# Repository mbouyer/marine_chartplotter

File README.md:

Hardware and software for an opencpn-based chartplotter
The kardware has been designed with kicad 4.0.x
The chartplotter is built around a A20-based single-board computer
from Olimex (https://www.olimex.com/Products/OLinuXino/A20/A20-OLinuXIno-LIME2/)
and a 15" TFT full HD display also from Olimex
(https://www.olimex.com/Products/OLinuXino/LCD/LCD-OLinuXino-15.6FHD)

The hardware consist of 4 boards
- a breakout board for the Lime2, also providing power supplies,
  an audio amplifier, RS422 and CAN interfaces, and a I2C connection to
  a PIC18 for power management and TOD clock.
- a board holding buttons
- a board holding a GPS module
- a board for connections to other electronic equipements (VHF, sensors, ...)
  via a single flat cable.

for more details see the wiki: https://github.com/mbouyer/marine_chartplotter/wiki

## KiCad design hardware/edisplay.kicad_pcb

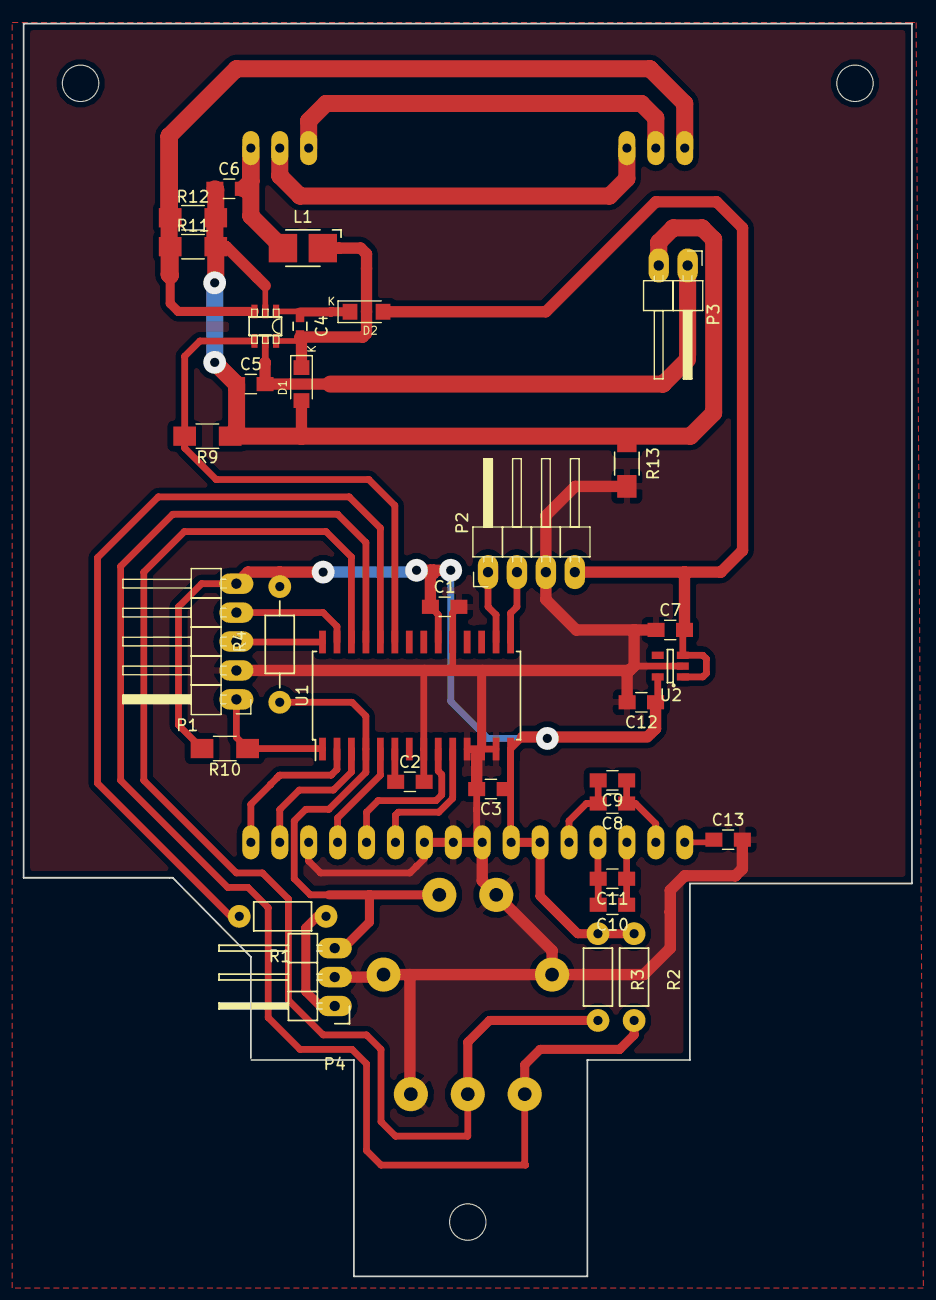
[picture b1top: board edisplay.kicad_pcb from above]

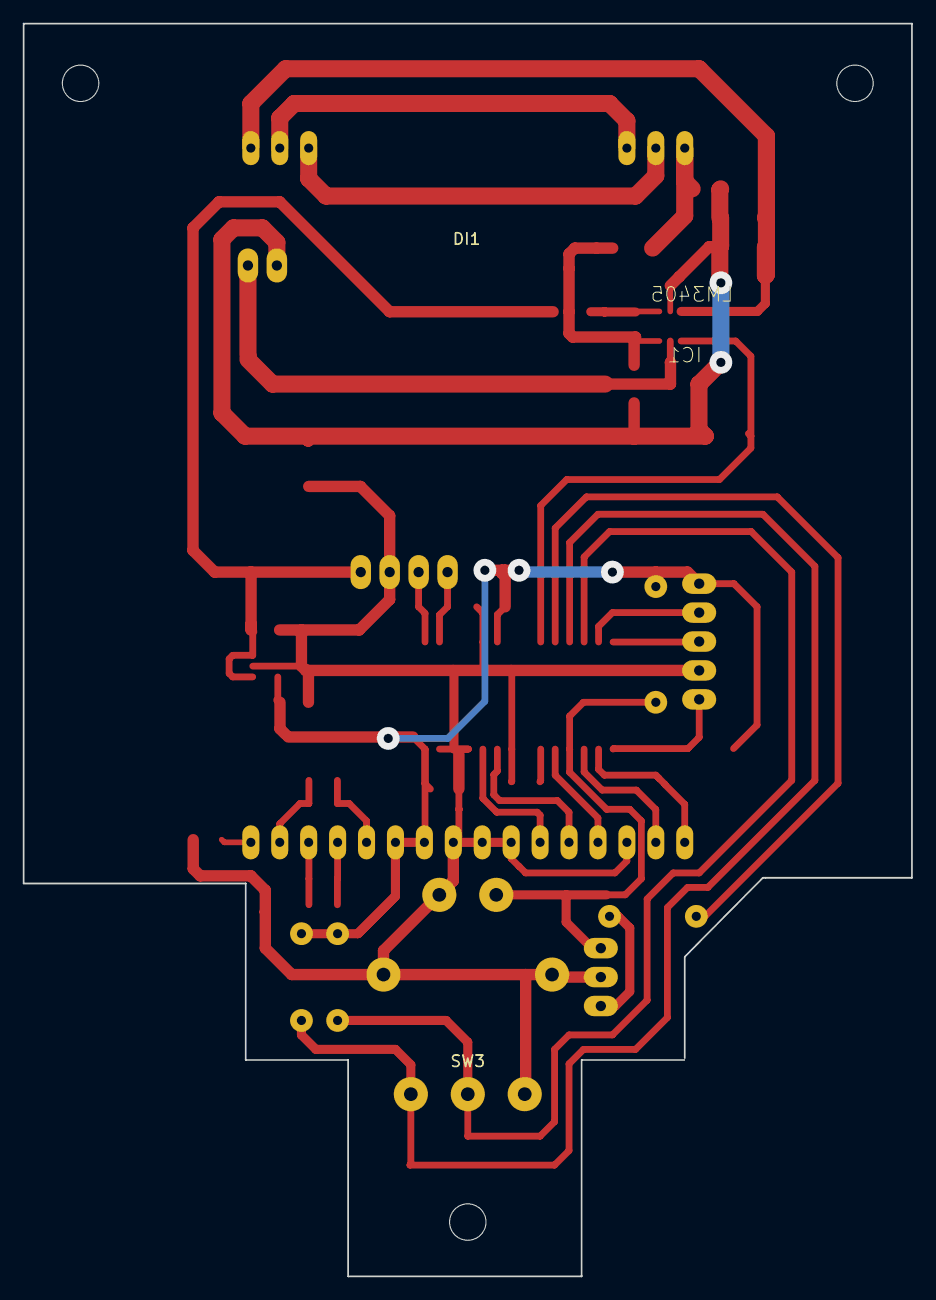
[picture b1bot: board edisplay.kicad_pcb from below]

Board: 2 copper layers, 78.0 x 110.0 mm, 34 parts (2 on the bottom side), 33 nets.

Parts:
C1, C3, C5, C6, C7, C8, C9, C10, C11, C12, C13: 1µF; C_0805_HandSoldering
C2: 10µF; C_0805_HandSoldering
C4: 0.1µF; C_0603_HandSoldering
D1, D2: SL02; DO-219AB
DI1: EADOGXL160-7
IC1: LM3405; texas-local-SOT23-06
L1: 68µH; Inductor_1212
P1: CONN_01X05; Pin_Header_Angled_1x05_Pitch2.54mm
P2: CONN_01X04; Pin_Header_Angled_1x04_Pitch2.54mm
P3: CONN_01X02; Pin_Header_Angled_1x02_Pitch2.54mm
P4: CONN_01X03; Pin_Header_Angled_1x03
R1: 330; Resistor_Horizontal_RM7mm
R2, R3: 10K; Resistor_Horizontal_RM7mm
R4: 10K; Resistor_Horizontal_RM10mm
R9: 10K; R_1206_HandSoldering
R10: 1K; R_1206_HandSoldering
R11, R12: 5.1; R_1206_HandSoldering
R13: 330; R_1206_HandSoldering
SW3: ROTARY_ENCODER_SWITCH; PEC16_S
U1: PIC18F26J53; SOIC-28W_7.5x17.9mm_Pitch1.27mm
U2: LP3990MF; SOT-23-5

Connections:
+3V3: C1.1, C3.1, C12.1, DI1.22, DI1.23, P1.5, R2.1, R3.1, R4.2, R10.2, U1.14, U1.20, U2.5
+5V: C7.2, D2.2, P2.4, U2.1, U2.3
+12V: C5.2, IC1.5, P3.1
GND: C1.2, C2.2, C3.2, C7.1, C12.2, C13.2, DI1.24, DI1.25, DI1.26, DI1.30, P1.2, P2.3, P4.2, R13.2, SW3.2, SW3.4, U1.8, U1.11, U1.12, U1.13, U1.19, U2.2
GNDA: C5.1, C6.1, D1.2, IC1.2, P3.2, R9.1, R11.2, R12.2, R13.1
unnamed: C2.1, U1.6
unnamed: C4.1, D2.1, IC1.1
unnamed: C4.2, D1.1, IC1.6, L1.1
unnamed: C6.2, DI1.1, L1.2
unnamed: C8.1, C9.1, DI1.18
unnamed: C8.2, C9.2, DI1.21
unnamed: C10.1, C11.1, DI1.19
unnamed: C10.2, C11.2, DI1.20
unnamed: C13.1, DI1.17
unnamed: DI1.2, DI1.14
unnamed: DI1.3, DI1.15
unnamed: DI1.16, IC1.3, R11.1, R12.1
unnamed: DI1.27, U1.10
unnamed: DI1.28, U1.9
unnamed: DI1.29, U1.5
unnamed: DI1.31, U1.3
unnamed: DI1.32, U1.2
unnamed: IC1.4, R9.2, U1.23
unnamed: P1.1, R10.1, U1.1
unnamed: P1.3, U1.28
unnamed: P1.4, U1.27
unnamed: P2.1, U1.16
unnamed: P2.2, U1.15
unnamed: P4.1, R1.1
unnamed: P4.3, R4.1, SW3.5, U1.4
unnamed: R1.2, U1.24
unnamed: R2.2, SW3.1, U1.25
unnamed: R3.2, SW3.3, U1.26

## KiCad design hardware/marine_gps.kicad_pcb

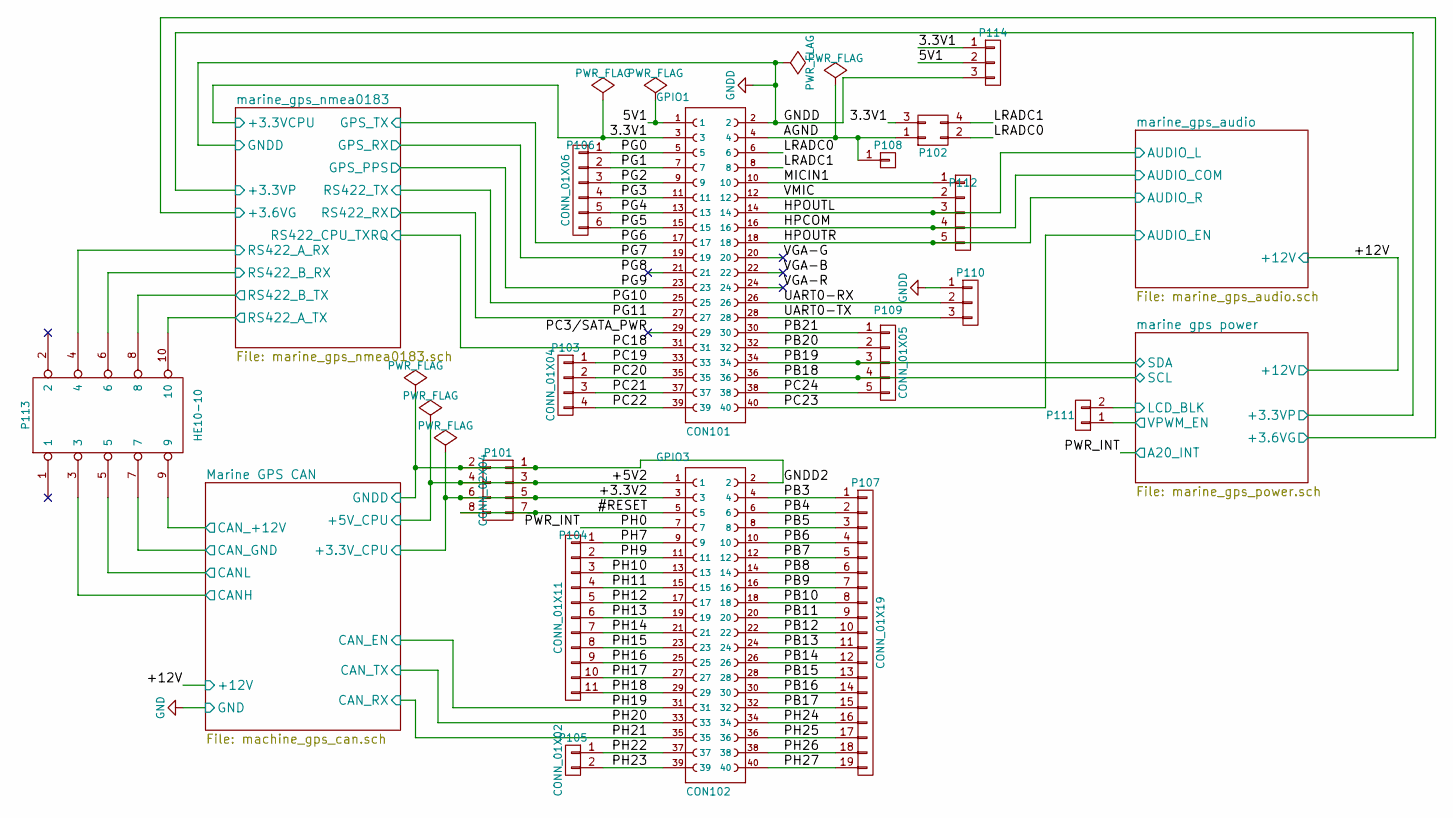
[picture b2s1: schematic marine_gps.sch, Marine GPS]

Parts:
CON101: GPIO1; A10_OLIMEXINO_LIME_SHIELD_1-YA-V36P-2X20-LF
CON102: GPIO3; A10_OLIMEXINO_LIME_SHIELD_1-YA-V36P-2X20-LF
P101: CONN_02X04; Pin_Header_Angled_2x04
P102: CONN_02X02; Pin_Header_Angled_2x02
P103: CONN_01X04; Pin_Header_Straight_1x04
P104: CONN_01X11; Pin_Header_Straight_1x11
P105, P111: CONN_01X02; Pin_Header_Straight_1x02
P106: CONN_01X06; Pin_Header_Straight_1x06
P107: CONN_01X19; Pin_Header_Straight_1x19
P108: CONN_01X01; Pin_Header_Straight_1x01
P109, P112: CONN_01X05; Pin_Header_Straight_1x05
P110: CONN_01X03; Pin_Header_Straight_1x03
P113: HE10-10; HE10-10C
P114: CONN_01X03; Pin_Header_Angled_1x03

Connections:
/5V1: CON101.1, P114.2
/#RESET: CON102.5, P101.7, P101.8
/AGND: CON101.4, P102.1, P108.1
/LRADC0: CON101.6, P102.2
/LRADC1: CON101.8, P102.4
/MICIN1: CON101.10, P112.1
/Marine GPS CAN/+3.3V_CPU: CON102.3, P101.5, P101.6; also elsewhere on the board
/Marine GPS CAN/+5V_CPU: CON102.1, P101.3, P101.4; also elsewhere on the board
/Marine GPS CAN/CANH: P113.3; also elsewhere on the board
/Marine GPS CAN/CANL: P113.5; also elsewhere on the board
/Marine GPS CAN/CAN_+12V: P113.9; also elsewhere on the board
/Marine GPS CAN/CAN_EN: CON102.31; also elsewhere on the board
/Marine GPS CAN/CAN_RX: CON102.35; also elsewhere on the board
/Marine GPS CAN/CAN_TX: CON102.33; also elsewhere on the board
/Marine GPS CAN/GNDD: CON102.2, P101.1, P101.2; also elsewhere on the board
/PB3: CON102.4, P107.1
/PB4: CON102.6, P107.2
/PB5: CON102.8, P107.3
/PB6: CON102.10, P107.4
/PB7: CON102.12, P107.5
/PB8: CON102.14, P107.6
/PB9: CON102.16, P107.7
/PB10: CON102.18, P107.8
/PB11: CON102.20, P107.9
/PB12: CON102.22, P107.10
/PB13: CON102.24, P107.11
/PB14: CON102.26, P107.12
/PB15: CON102.28, P107.13
/PB16: CON102.30, P107.14
/PB17: CON102.32, P107.15
/PB20: CON101.32, P109.2
/PB21: CON101.30, P109.1
/PC3/SATA_PWR: CON101.29
/PC19: CON101.33, P103.1
/PC20: CON101.35, P103.2
/PC21: CON101.37, P103.3
/PC22: CON101.39, P103.4
/PC24: CON101.38, P109.5
/PG0: CON101.5, P106.1
/PG1: CON101.7, P106.2
/PG2: CON101.9, P106.3
/PG3: CON101.11, P106.4
/PG4: CON101.13, P106.5
/PG5: CON101.15, P106.6
/PG8: CON101.21
/PH7: CON102.9, P104.1
/PH9: CON102.11, P104.2
/PH10: CON102.13, P104.3
/PH11: CON102.15, P104.4
/PH12: CON102.17, P104.5
/PH13: CON102.19, P104.6
/PH14: CON102.21, P104.7
/PH15: CON102.23, P104.8
/PH16: CON102.25, P104.9
/PH17: CON102.27, P104.10
/PH18: CON102.29, P104.11
/PH22: CON102.37, P105.1
/PH23: CON102.39, P105.2
/PH24: CON102.34, P107.16
/PH25: CON102.36, P107.17
/PH26: CON102.38, P107.18
/PH27: CON102.40, P107.19
/UART0-RX: CON101.26, P110.2
/UART0-TX: CON101.28, P110.3
/VGA-B: CON101.22
/VGA-G: CON101.20
/VGA-R: CON101.24
/VMIC: CON101.12, P112.2
/marine gps power/A20_INT: CON102.7; also elsewhere on the board
/marine gps power/LCD_BLK: P111.2; also elsewhere on the board
/marine gps power/SCL: CON101.36, P109.4; also elsewhere on the board
/marine gps power/SDA: CON101.34, P109.3; also elsewhere on the board
/marine gps power/VPWM_EN: P111.1; also elsewhere on the board
/marine_gps_audio/AUDIO_COM: CON101.16, P112.4; also elsewhere on the board
/marine_gps_audio/AUDIO_EN: CON101.40; also elsewhere on the board
/marine_gps_audio/AUDIO_L: CON101.14, P112.3; also elsewhere on the board
/marine_gps_audio/AUDIO_R: CON101.18, P112.5; also elsewhere on the board
/marine_gps_nmea0183/GPS_PPS: CON101.23; also elsewhere on the board
/marine_gps_nmea0183/GPS_RX: CON101.19; also elsewhere on the board
/marine_gps_nmea0183/GPS_TX: CON101.17; also elsewhere on the board
/marine_gps_nmea0183/RS422_A_RX: P113.4; also elsewhere on the board
/marine_gps_nmea0183/RS422_A_TX: P113.10; also elsewhere on the board
/marine_gps_nmea0183/RS422_B_RX: P113.6; also elsewhere on the board
/marine_gps_nmea0183/RS422_B_TX: P113.8; also elsewhere on the board
/marine_gps_nmea0183/RS422_CPU_TXRQ: CON101.31; also elsewhere on the board
/marine_gps_nmea0183/RS422_RX: CON101.27; also elsewhere on the board
/marine_gps_nmea0183/RS422_TX: CON101.25; also elsewhere on the board
GND: P113.7; also elsewhere on the board
GND2: CON101.2, P110.1, P114.3; also elsewhere on the board
VCC2: CON101.3, P102.3, P114.1; also elsewhere on the board

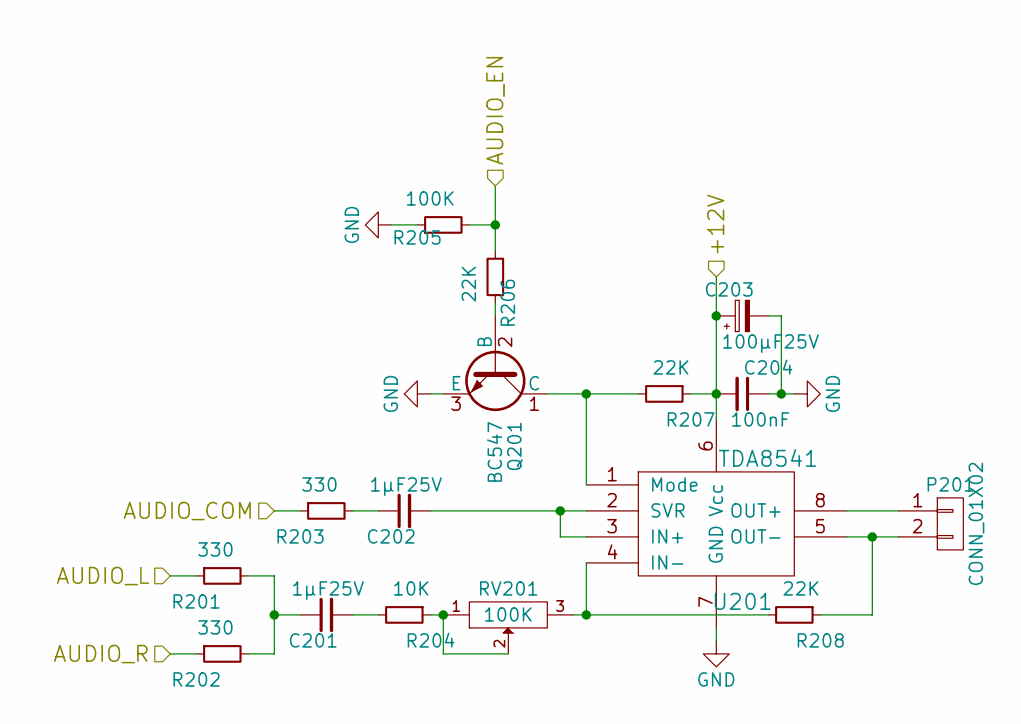
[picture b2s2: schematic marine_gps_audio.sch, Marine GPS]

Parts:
C201, C202: 1µF25V; C_0805
C203: 100µF25V; C_Radial_D6.3_L11.2_P2.5
C204: 100nF; C_0805
P201: CONN_01X02; Pin_Header_Straight_1x02
Q201: BC547; TO-92_Molded_Narrow
R201, R202, R203: 330; Resistor_Horizontal_RM15mm
R204: 10K; Resistor_Horizontal_RM15mm
R205: 100K; Resistor_Horizontal_RM10mm
R206: 22K; Resistor_Horizontal_RM10mm
R207, R208: 22K; Resistor_Horizontal_RM15mm
RV201: 100K; CB10LV
U201: TDA8541; SOIC-8-N

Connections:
+12V: C203.1, C204.2, R207.1, U201.6 (Vcc); also elsewhere on the board
/marine_gps_audio/AUDIO_COM: R203.1; also elsewhere on the board
/marine_gps_audio/AUDIO_EN: R205.2, R206.2; also elsewhere on the board
/marine_gps_audio/AUDIO_L: R201.1; also elsewhere on the board
/marine_gps_audio/AUDIO_R: R202.1; also elsewhere on the board
GND: C203.2, C204.1, Q201.3 (E), R205.1, U201.7 (GND); also elsewhere on the board
unnamed: C201.1, R201.2, R202.2
unnamed: C201.2, R204.2
unnamed: C202.1, R203.2
unnamed: C202.2, U201.2 (SVR), U201.3 (IN+)
unnamed: P201.1, U201.8 (OUT+)
unnamed: P201.2, R208.1, U201.5 (OUT-)
unnamed: Q201.1 (C), R207.2, U201.1 (Mode)
unnamed: Q201.2 (B), R206.1
unnamed: R204.1, RV201.1, RV201.2
unnamed: R208.2, RV201.3, U201.4 (IN-)

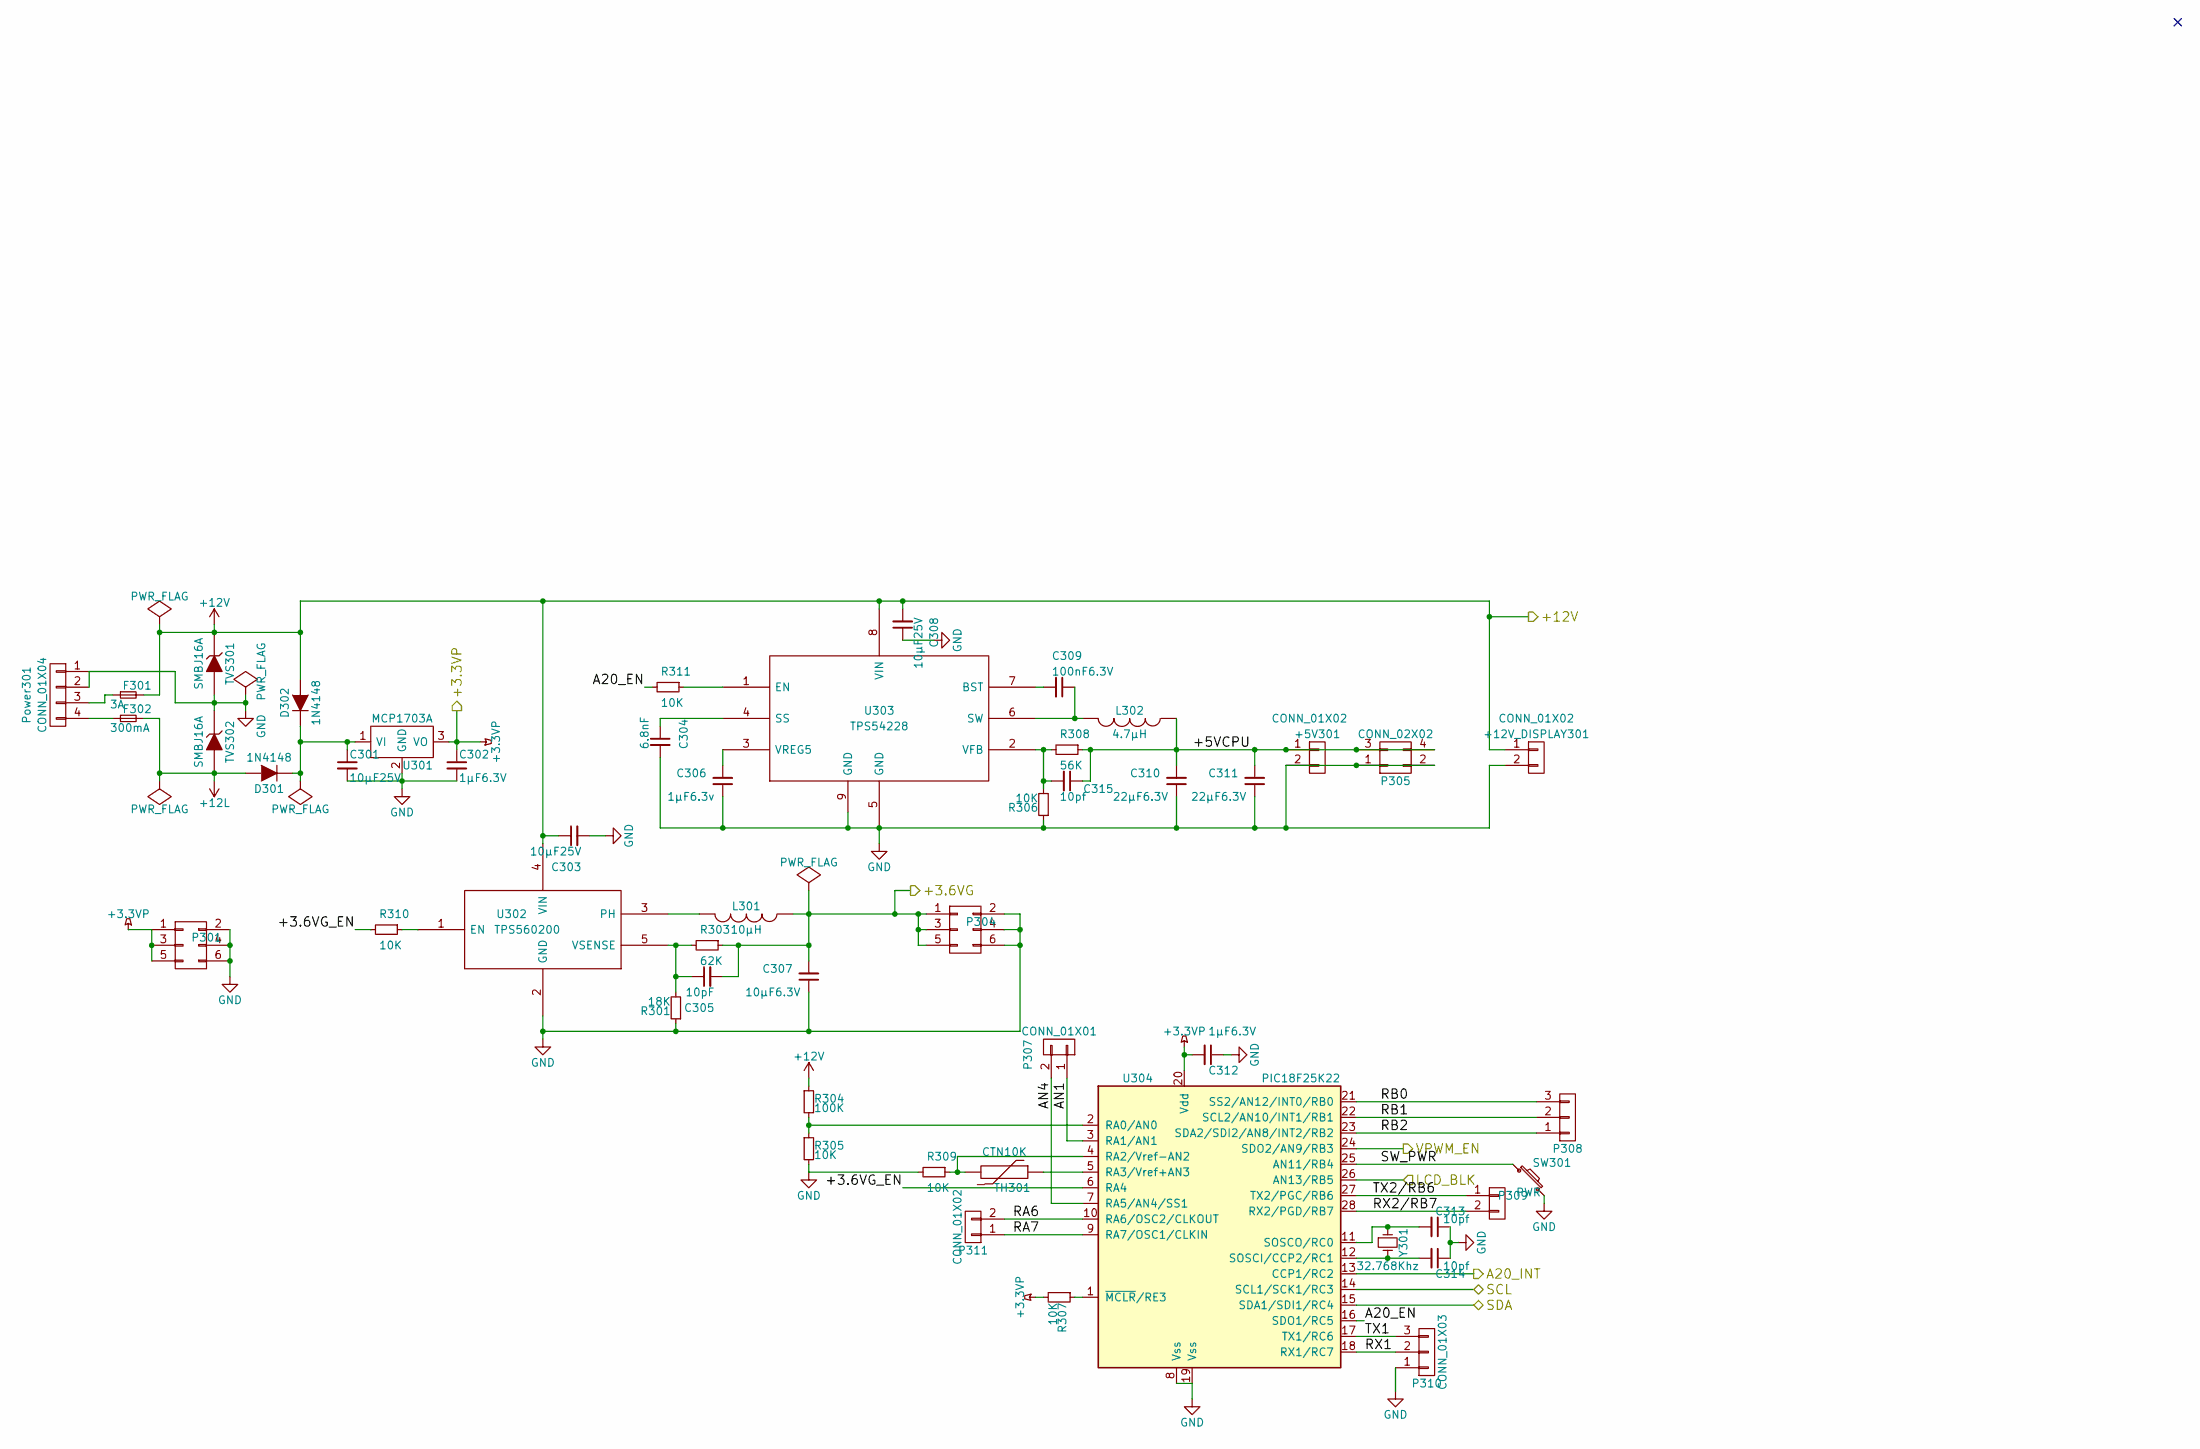
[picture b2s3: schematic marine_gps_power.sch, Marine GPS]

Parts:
+5V301, +12V_DISPLAY301: CONN_01X02; Pin_Header_Straight_1x02
C301, C303, C308: 10µF25V; C_1210
C302, C312: 1µF6.3V; C_0805
C304: 6.8nF; C_0603_HandSoldering
C305: 10pF; C_0603_HandSoldering
C306: 1µF6.3v; C_0805
C307: 10µF6.3V; C_1210
C309: 100nF6.3V; C_0805
C310, C311: 22µF6.3V; C_1210
C313, C314, C315: 10pf; C_0603_HandSoldering
D301, D302: 1N4148; Diode_DO-35_SOD27_Horizontal_RM10
F301: 3A; Fuseholder5x20_horiz_SemiClosed_Casing10x22.5mm
F302: 300mA; Fuseholder5x20_horiz_SemiClosed_Casing10x22.5mm
L301: 10µH; Choke_SMD_7.3x7.3_H4.5
L302: 4.7µH; Choke_SMD_10.4x10.4_H4.8
P301, P304: CONN_02X03; Pin_Header_Angled_2x03
P305: CONN_02X02; Pin_Header_Angled_2x02
P307: CONN_01X01; Pin_Header_Straight_1x02
P308, P310: CONN_01X03; Pin_Header_Angled_1x03
P309, P311: CONN_01X02; Pin_Header_Straight_1x02
Power301: CONN_01X04; minifit-4
R301: 18K; Resistor_Horizontal_RM15mm
R303: 62K; Resistor_Horizontal_RM15mm
R304: 100K; Resistor_Horizontal_RM10mm
R305, R310, R311: 10K; Resistor_Horizontal_RM10mm
R306, R307: 10K; R_1210_HandSoldering
R308: 56K; R_1210_HandSoldering
R309: 10K; Resistor_Horizontal_RM15mm
SW301: PWR; Pin_Header_Angled_1x02
TH301: CTN10K; Pin_Header_Straight_1x02
TVS301, TVS302: SMBJ16A; DO-214AB
U301: MCP1703A; SOT-223-Tto2
U302: TPS560200; SOT-23-5
U303: TPS54228; SOIC-8-1EP_3.9x4.9mm_Pitch1.27mm
U304: PIC18F25K22; DIP-28_W7.62mm_LongPads
Y301: 32.768Khz; CMR200T

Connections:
+3.3VP: C302.1, C312.2, P301.1, P301.3, P301.5, R307.2, U301.3 (VO), U304.20 (Vdd); also elsewhere on the board
+12L: D301.2 (A), F302.2, TVS302.2 (A)
+12V: +12V_DISPLAY301.1, C303.1, C308.2, D302.2 (A), F301.2, R304.1, TVS301.1 (K), U302.4 (VIN), U303.8 (VIN); also elsewhere on the board
/marine gps power/+3.6VG_EN: R310.2, U304.6 (RA4)
/marine gps power/+5VCPU: +5V301.1, C310.2, C311.2, C315.1, L302.1, P305.3, P305.4, R308.1
/marine gps power/A20_EN: R311.2, U304.16 (SDO1/RC5)
/marine gps power/A20_INT: U304.13 (CCP1/RC2); also elsewhere on the board
/marine gps power/AN1: P307.1, U304.3 (RA1/AN1)
/marine gps power/AN4: P307.2, U304.7 (RA5/AN4/SS1)
/marine gps power/LCD_BLK: U304.26 (AN13/RB5); also elsewhere on the board
/marine gps power/RA6: P311.2, U304.10 (RA6/OSC2/CLKOUT)
/marine gps power/RA7: P311.1, U304.9 (RA7/OSC1/CLKIN)
/marine gps power/RB0: P308.3, U304.21 (SS2/AN12/INT0/RB0)
/marine gps power/RB1: P308.2, U304.22 (SCL2/AN10/INT1/RB1)
/marine gps power/RB2: P308.1, U304.23 (SDA2/SDI2/AN8/INT2/RB2)
/marine gps power/RX1: P310.2, U304.18 (RX1/RC7)
/marine gps power/RX2/RB7: P309.2, U304.28 (RX2/PGD/RB7)
/marine gps power/SCL: U304.14 (SCL1/SCK1/RC3); also elsewhere on the board
/marine gps power/SDA: U304.15 (SDA1/SDI1/RC4); also elsewhere on the board
/marine gps power/SW_PWR: SW301.1, U304.25 (AN11/RB4)
/marine gps power/TX1: P310.3, U304.17 (TX1/RC6)
/marine gps power/TX2/RB6: P309.1, U304.27 (TX2/PGC/RB6)
/marine gps power/VPWM_EN: U304.24 (SDO2/AN9/RB3); also elsewhere on the board
GND: +5V301.2, +12V_DISPLAY301.2, C301.2, C302.2, C303.2, C304.2, C306.1, C307.1, C308.1, C310.1, C311.1, C312.1, C313.1, C314.1, P301.2, P301.4, P301.6, P304.2, P304.4, P304.6, P305.1, P305.2, P310.1, Power301.1, Power301.2, R301.1, R305.2, R306.1, R309.2, SW301.2, TVS301.2 (A), TVS302.1 (K), U301.2 (GND), U302.2 (GND), U303.5 (GND), U303.9 (GND), U304.8 (Vss), U304.19 (Vss); also elsewhere on the board
unnamed: C301.1, D301.1 (K), D302.1 (K), U301.1 (VI)
unnamed: C304.1, U303.4 (SS)
unnamed: C305.1, R301.2, R303.2, U302.5 (VSENSE)
unnamed: C306.2, U303.3 (VREG5)
unnamed: C309.1, L302.2, U303.6 (SW)
unnamed: C309.2, U303.7 (BST)
unnamed: C313.2, U304.11 (SOSCO/RC0), Y301.1
unnamed: C314.2, U304.12 (SOSCI/CCP2/RC1), Y301.2
unnamed: C315.2, R306.2, R308.2, U303.2 (VFB)
unnamed: F301.1, Power301.3
unnamed: F302.1, Power301.4
unnamed: L301.2, U302.3 (PH)
unnamed: R304.2, R305.1, U304.2 (RA0/AN0)
unnamed: R307.1, U304.1 (~MCLR~/RE3)
unnamed: R309.1, TH301.2, U304.4 (RA2/Vref-AN2)
unnamed: R310.1, U302.1 (EN)
unnamed: R311.1, U303.1 (EN)
unnamed: TH301.1, U304.5 (RA3/Vref+AN3)
VCC: C305.2, C307.2, L301.1, P304.1, P304.3, P304.5, R303.1; also elsewhere on the board

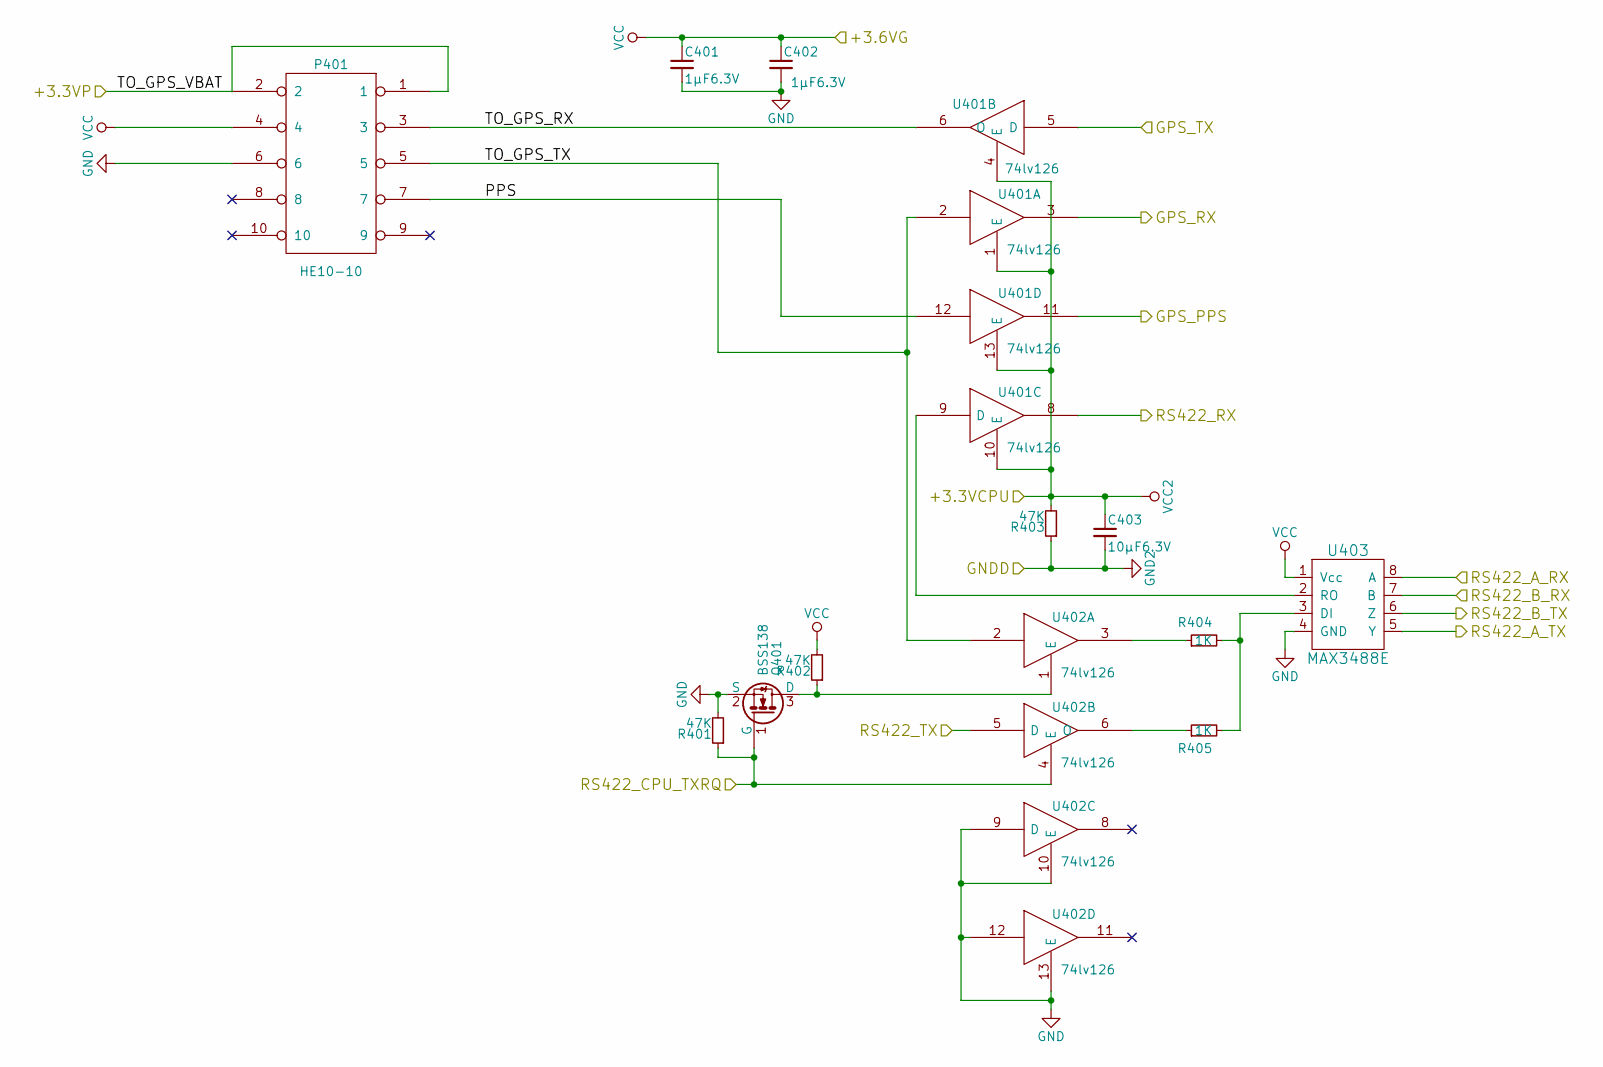
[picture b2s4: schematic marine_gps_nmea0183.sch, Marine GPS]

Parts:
C401, C402: 1µF6.3V; C_1210
C403: 10µF6.3V; C_1210
P401: HE10-10; HE10-10C
Q401: BSS138; SOT-23
R401, R402, R403: 47K; Resistor_Horizontal_RM15mm
R404, R405: 1K; Resistor_Horizontal_RM15mm
U401, U402: 74lv126; SOIC-14_3.9x8.7mm_Pitch1.27mm
U403: MAX3488E; SOIC-8_3.9x4.9mm_Pitch1.27mm

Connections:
+3.3VP: P401.1, P401.2; also elsewhere on the board
/marine_gps_nmea0183/GPS_PPS: U401.11; also elsewhere on the board
/marine_gps_nmea0183/GPS_RX: U401.3; also elsewhere on the board
/marine_gps_nmea0183/GPS_TX: U401.5 (D); also elsewhere on the board
/marine_gps_nmea0183/PPS: P401.7, U401.12
/marine_gps_nmea0183/RS422_A_RX: U403.8 (A); also elsewhere on the board
/marine_gps_nmea0183/RS422_A_TX: U403.5 (Y); also elsewhere on the board
/marine_gps_nmea0183/RS422_B_RX: U403.7 (B); also elsewhere on the board
/marine_gps_nmea0183/RS422_B_TX: U403.6 (Z); also elsewhere on the board
/marine_gps_nmea0183/RS422_CPU_TXRQ: Q401.1 (G), R401.1, U402.4 (E); also elsewhere on the board
/marine_gps_nmea0183/RS422_RX: U401.8; also elsewhere on the board
/marine_gps_nmea0183/RS422_TX: U402.5 (D); also elsewhere on the board
/marine_gps_nmea0183/TO_GPS_RX: P401.3, U401.6 (O)
/marine_gps_nmea0183/TO_GPS_TX: P401.5, U401.2, U402.2
GND: C401.2, C402.2, P401.6, Q401.2 (S), R401.2, U402.7 (GND), U402.9 (D), U402.10 (E), U402.12, U402.13 (E), U403.4 (GND); also elsewhere on the board
GND2: C403.2, R403.1, U401.7 (GND2); also elsewhere on the board
unnamed: Q401.3 (D), R402.1, U402.1 (E)
unnamed: R404.1, U402.3
unnamed: R404.2, R405.2, U403.3 (DI)
unnamed: R405.1, U402.6 (O)
unnamed: U401.9 (D), U403.2 (RO)
VCC: C401.1, C402.1, P401.4, R402.2, U402.14 (VCC), U403.1 (Vcc); also elsewhere on the board
VCC2: C403.1, R403.2, U401.1 (E), U401.4 (E), U401.10 (E), U401.13 (E), U401.14 (VCC2); also elsewhere on the board

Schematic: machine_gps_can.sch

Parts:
C501, C502: 1µF6.3V; C_0805
P501: CONN_01X02; Pin_Header_Straight_1x02
Q501, Q502: BSS138; SOT-23
Q503: DMG2307L; SOT-23
R501: 47K; Resistor_Horizontal_RM15mm
R502: 47K; Resistor_Horizontal_RM10mm
U501: MCP2562; DIP-8_W7.62mm

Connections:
+12V: Q503.2, R502.1; also elsewhere on the board
/Marine GPS CAN/+3.3V_CPU: C502.2, U501.5 (VIO); also elsewhere on the board
/Marine GPS CAN/+5V_CPU: C501.1, U501.3 (VDD); also elsewhere on the board
/Marine GPS CAN/CANH: U501.7 (CANH); also elsewhere on the board
/Marine GPS CAN/CANL: U501.6 (CANL); also elsewhere on the board
/Marine GPS CAN/CAN_+12V: P501.2; also elsewhere on the board
/Marine GPS CAN/CAN_EN: Q501.1 (G), Q502.1 (G), R501.2; also elsewhere on the board
/Marine GPS CAN/CAN_RX: U501.4 (RXD); also elsewhere on the board
/Marine GPS CAN/CAN_TX: U501.1 (TXD); also elsewhere on the board
/Marine GPS CAN/GNDD: C501.2, C502.1, Q501.2 (S), Q502.2 (S), R501.1, U501.2 (VSS); also elsewhere on the board
unnamed: P501.1, Q503.3
unnamed: Q501.3 (D), U501.8 (STB)
unnamed: Q502.3 (D), Q503.1, R502.2

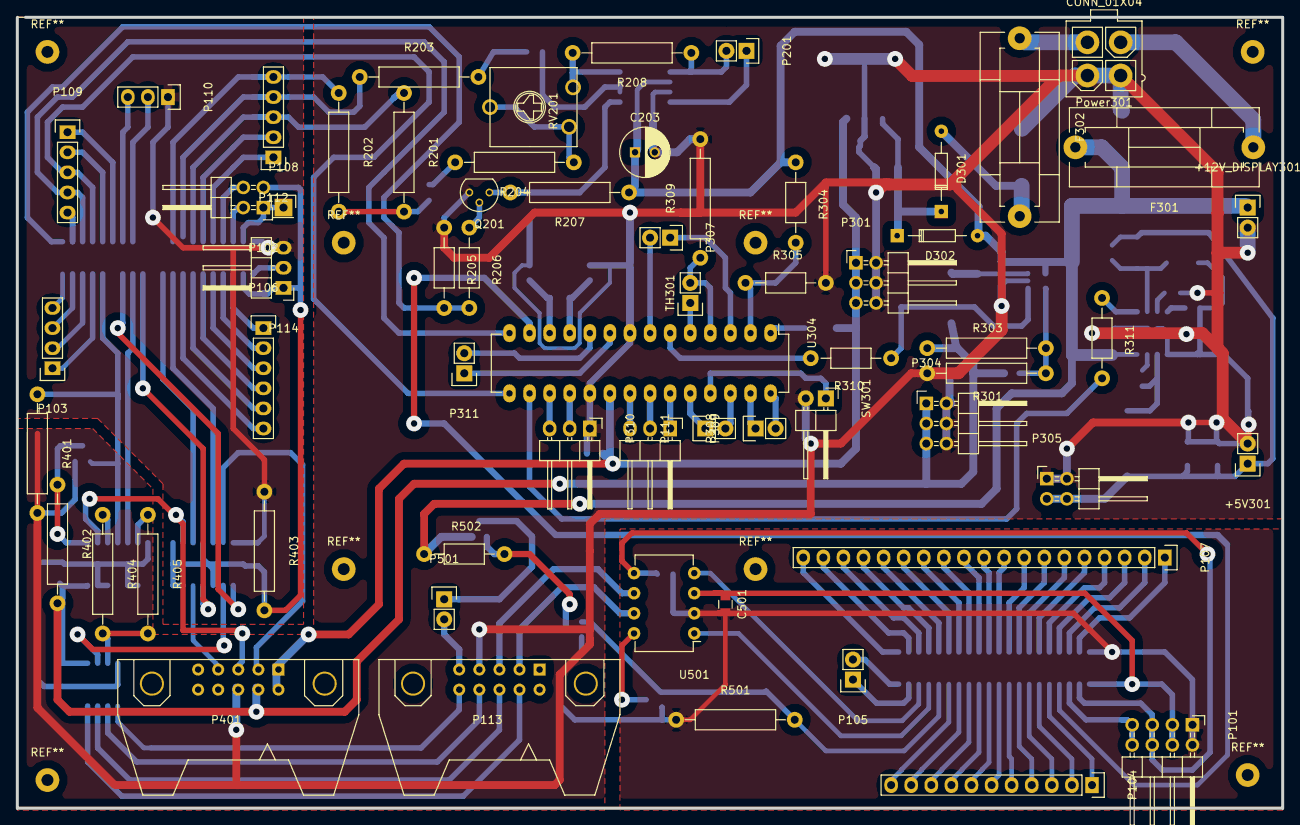
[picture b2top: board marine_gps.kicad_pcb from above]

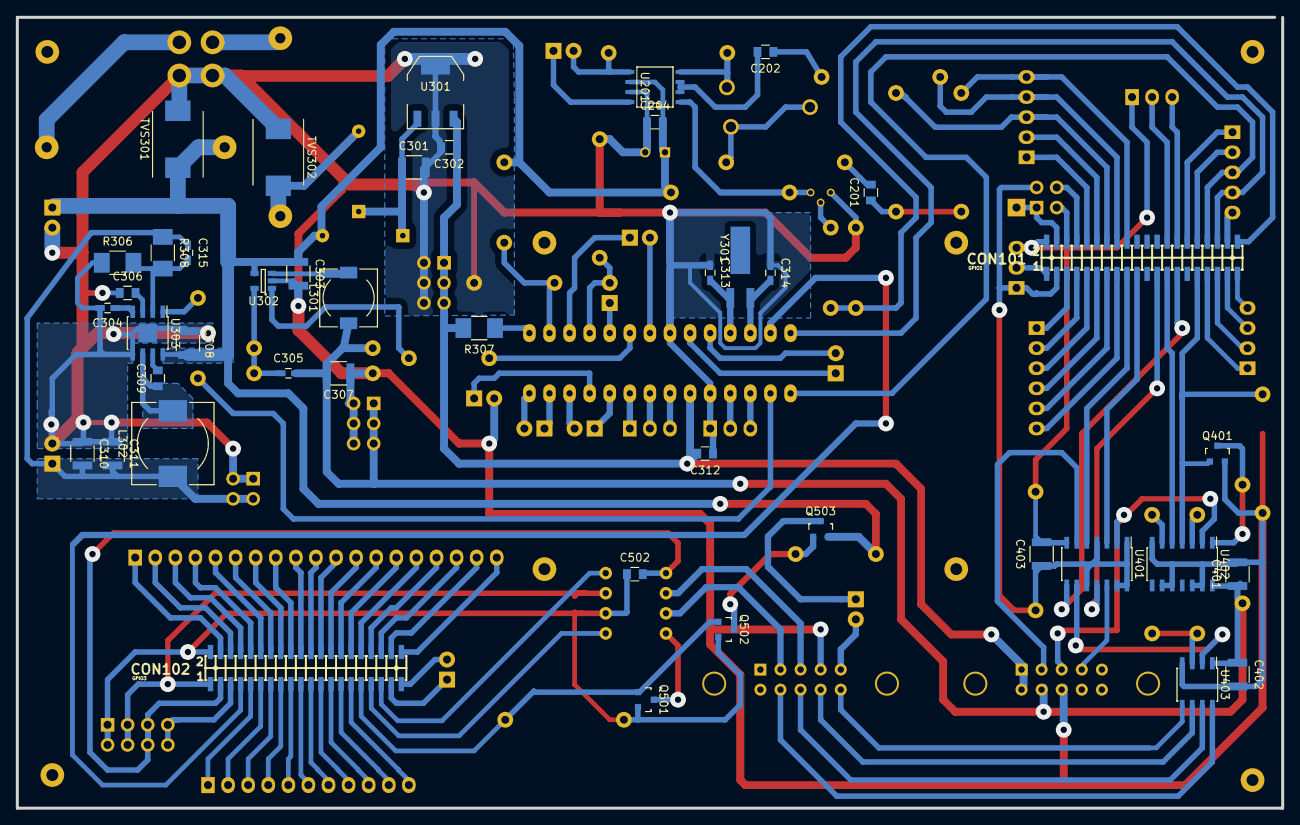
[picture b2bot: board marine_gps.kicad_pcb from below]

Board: 2 copper layers, 160.0 x 100.0 mm, 107 parts (43 on the bottom side), 143 nets.

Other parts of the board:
EU160: EuroBoard160mmX100mm
LIME2: LIME2; A20_OLIMEXINO_LIME_SHIELD

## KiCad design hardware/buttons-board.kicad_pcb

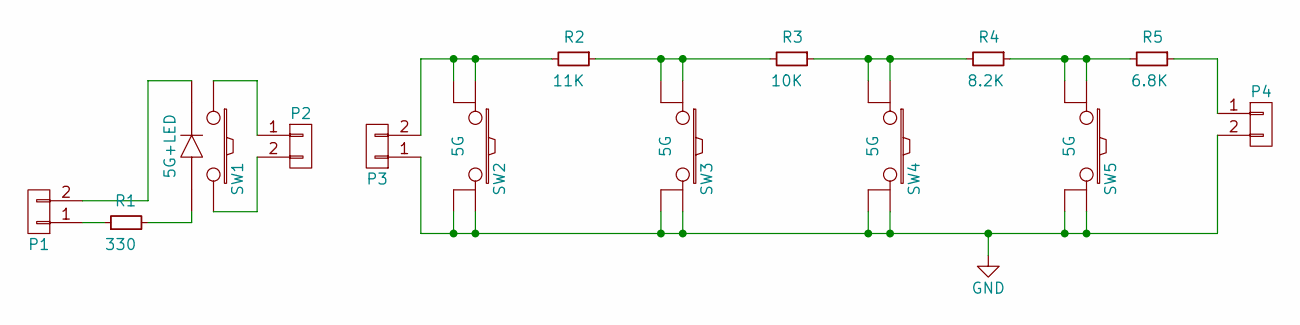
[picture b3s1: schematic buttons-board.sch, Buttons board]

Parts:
P1, P2, P3, P4: CONN_01X02; solder_2x5mm
R1: 330; Resistor_Horizontal_RM10mm
R2: 11K; Resistor_Horizontal_RM10mm
R3: 10K; Resistor_Horizontal_RM10mm
R4: 8.2K; Resistor_Horizontal_RM10mm
R5: 6.8K; Resistor_Horizontal_RM10mm
SW1: 5G+LED; 5G-1US
SW2, SW3, SW4, SW5: 5G; 5G-1US

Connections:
GND: P3.1, P4.2, SW2.3, SW2.4, SW3.3, SW3.4, SW4.3, SW4.4, SW5.3, SW5.4
unnamed: P1.1, R1.1
unnamed: P1.2, SW1.2 (-)
unnamed: P2.1, SW1.1
unnamed: P2.2, SW1.4
unnamed: P3.2, R2.2, SW2.1, SW2.2
unnamed: P4.1, R5.1
unnamed: R1.2, SW1.3 (+)
unnamed: R2.1, R3.2, SW3.1, SW3.2
unnamed: R3.1, R4.2, SW4.1, SW4.2
unnamed: R4.1, R5.2, SW5.1, SW5.2

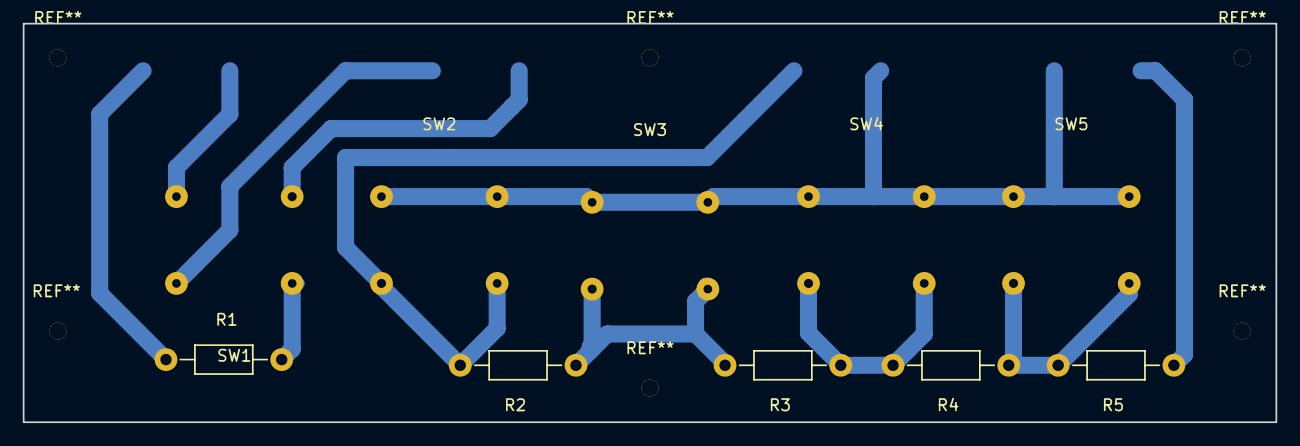
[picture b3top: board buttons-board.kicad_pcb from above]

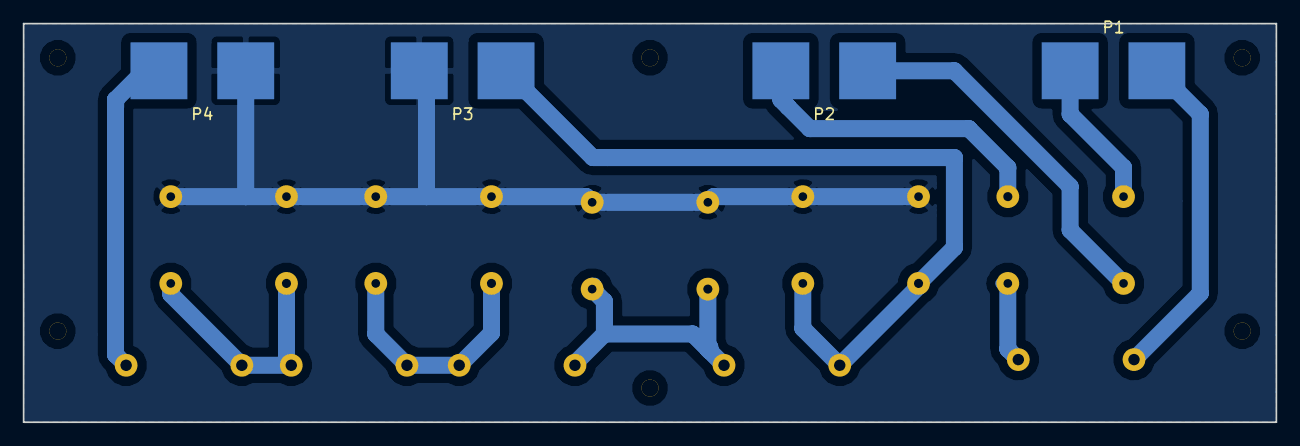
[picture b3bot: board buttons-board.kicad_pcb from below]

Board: 2 copper layers, 110.0 x 35.0 mm, 14 parts (4 on the bottom side), 11 nets.
